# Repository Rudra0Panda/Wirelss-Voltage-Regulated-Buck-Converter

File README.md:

# Wirelss-Voltage-Regulated-Buck-Converter

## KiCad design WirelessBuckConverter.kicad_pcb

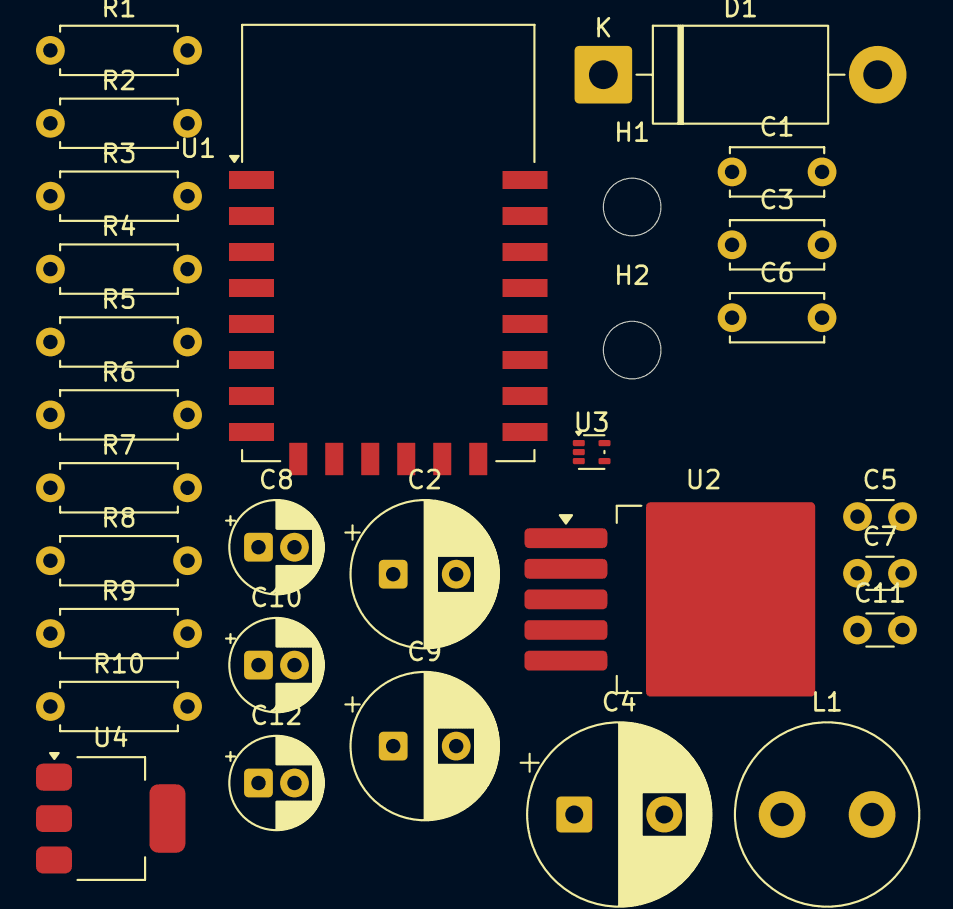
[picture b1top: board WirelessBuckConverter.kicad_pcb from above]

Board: 2 copper layers, 30 parts (0 on the bottom side), 15 nets, no tracks yet.

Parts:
C1, C3, C6: 105; C_Disc_D5.0mm_W2.5mm_P5.00mm
C2: 220uf; CP_Radial_D8.0mm_P3.50mm
C4: 330uf; CP_Radial_D10.0mm_P5.00mm
C5: 330uF; C_Disc_D3.0mm_W1.6mm_P2.50mm
C7, C11: 470pF; C_Disc_D3.0mm_W1.6mm_P2.50mm
C8, C12: 10uF; CP_Radial_D5.0mm_P2.00mm
C9: 47pf; CP_Radial_D8.0mm_P3.50mm
C10: 10uf; CP_Radial_D5.0mm_P2.00mm
D1: SB5H90; D_DO-201AD_P15.24mm_Horizontal
H1, H2: MountingHole_Pad; MountingHole_3.2mm_M3
L1: 47uH; L_Radial_D10.0mm_P5.00mm_Fastron_07M
R1: 15k; R_Axial_DIN0207_L6.3mm_D2.5mm_P7.62mm_Horizontal
R2: 3.3k; R_Axial_DIN0207_L6.3mm_D2.5mm_P7.62mm_Horizontal
R3, R5, R6, R7, R8, R9: 10k; R_Axial_DIN0207_L6.3mm_D2.5mm_P7.62mm_Horizontal
R4, R10: 1k; R_Axial_DIN0207_L6.3mm_D2.5mm_P7.62mm_Horizontal
U1: ESP-12E
U2: XL4015; TO-263-5_TabPin3
U3: NCS20071XV; SOT-553
U4: AMS1117-3.3; SOT-223-3_TabPin2

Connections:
3V3: C7.1, C9.1, C10.1, C12.1, R5.1, R6.1, R7.1, R8.1, U1.8 (VCC), U3.2 (V-), U4.2 (VO)
FBInput: C5.2, R1.2, R2.1, R10.1, U2.2 (FB), U3.3 (-), U3.4
GND: C2.2, C3.2, C4.2, C6.2, C7.2, C8.2, C9.2, C10.2, C11.2, C12.2, D1.2 (A), R2.2, R9.2, U1.15 (GND), U2.1 (GND), U3.5 (V+), U4.1 (GND)
unnamed: R5.2, U1.3 (EN)
unnamed: R7.2, U1.18 (GPIO0)
unnamed: R8.2, U1.17 (GPIO2)
unnamed: R9.1, U1.16 (GPIO15)
unnamed: R6.2, U1.1 (~RST)
unnamed: C1.2, U2.4 (VC)
unnamed: R3.1, U3.1 (+)
unnamed: C8.1, C11.1, R4.2, U4.3 (VI)
Output: C4.1, C5.1, C6.1, D1.1 (K), L1.1, L1.2, R1.1, R4.1, U2.3 (SW)
PWM: R3.2, U1.5 (GPIO14)
Vin: C1.1, C2.1, C3.1, U2.5 (VIN)
feedback: R10.2, U1.2 (ADC)

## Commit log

2026-03-06 Change WiFi SSID and password in main.cpp
